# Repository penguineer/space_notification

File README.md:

netz39_space_notification
=========================

Teilprojekte der Space Notification, z.B.

  * Ansteuerung Außenlampe
  * Ampel
  * Twitter-Notification

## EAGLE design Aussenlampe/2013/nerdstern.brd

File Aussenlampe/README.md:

netz39_space_notification
=========================

Außenlampe wird von Rene angeschlossen

Hier: Entwicklung des Steuerboards.

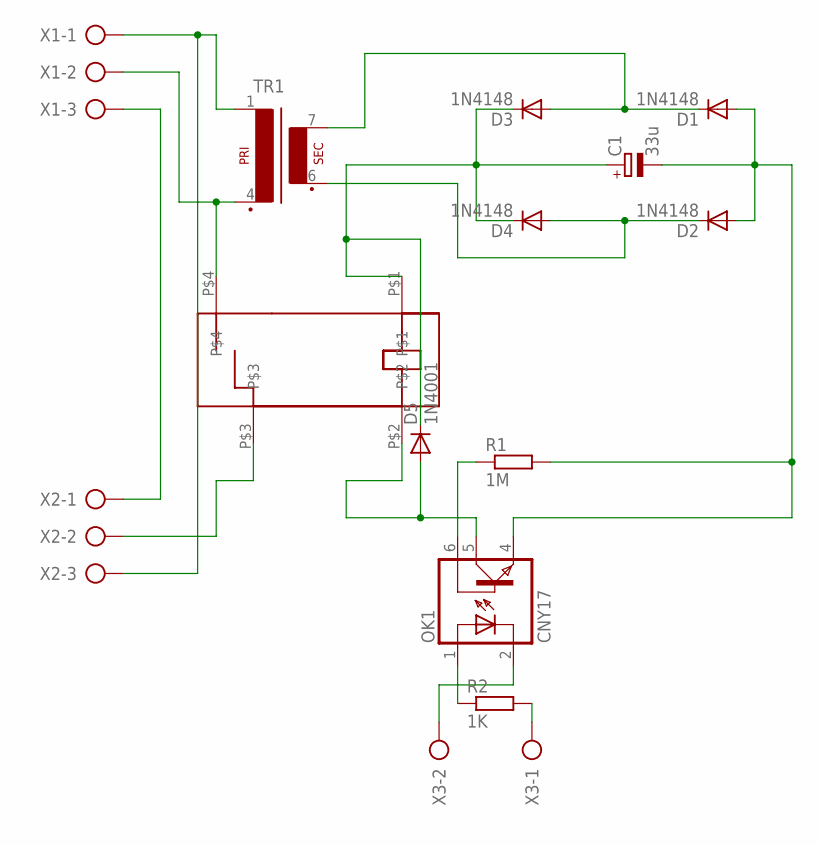
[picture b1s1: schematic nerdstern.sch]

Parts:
C1: 33u; E2-5
D1, D2, D3, D4: 1N4148; DO35-7
D5: 1N4001; DO35-7
OK1: CNY17; DIL06
R1: 1M; 0204/5
R2: 1K; 0204/5
TR1: EE20-1
U$1: JS_05_MN_KT
X1, X2: AK500/3
X3: AK500/2

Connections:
GND: C1.-, D1.A, D2.A, OK1.4 (EMI), R1.2
GND2: X1.3, X2.1
unnamed: TR1.4 (P2), U$1.P$4, X1.2
unnamed: U$1.P$3, X2.2
unnamed: TR1.1, X1.1, X2.3
unnamed: D1.C, D3.A, TR1.7 (S4)
unnamed: C1.+, D3.C, D4.C, D5.C, U$1.P$1
unnamed: D5.A, OK1.5 (COL), U$1.P$2
unnamed: D2.C, D4.A, TR1.6 (S3)
unnamed: OK1.1 (A), R2.1
unnamed: OK1.2 (C), X3.2
unnamed: OK1.6 (BAS), R1.1
unnamed: R2.2, X3.1

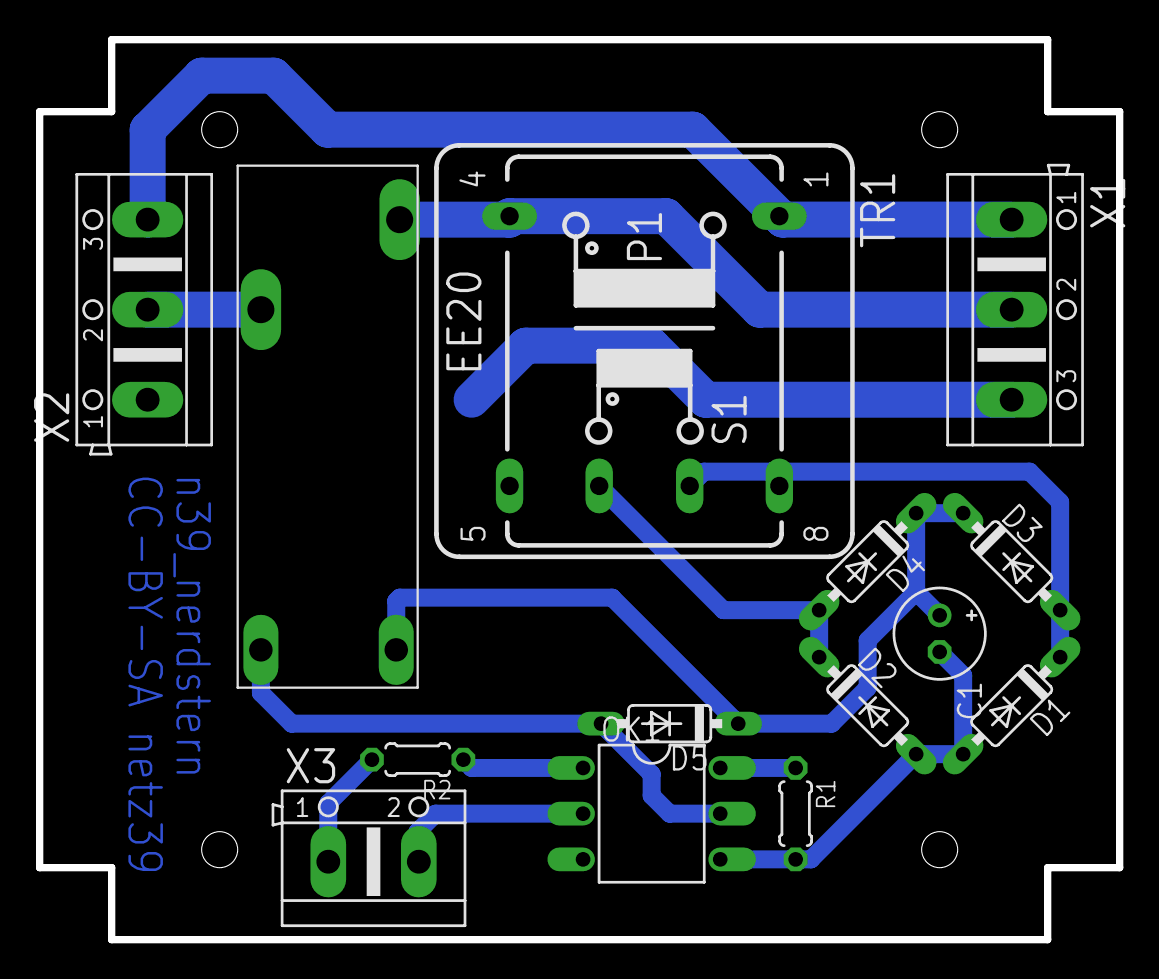
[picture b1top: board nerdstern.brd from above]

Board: 2 copper layers, 60.0 x 50.0 mm, 14 parts (0 on the bottom side), 13 nets.

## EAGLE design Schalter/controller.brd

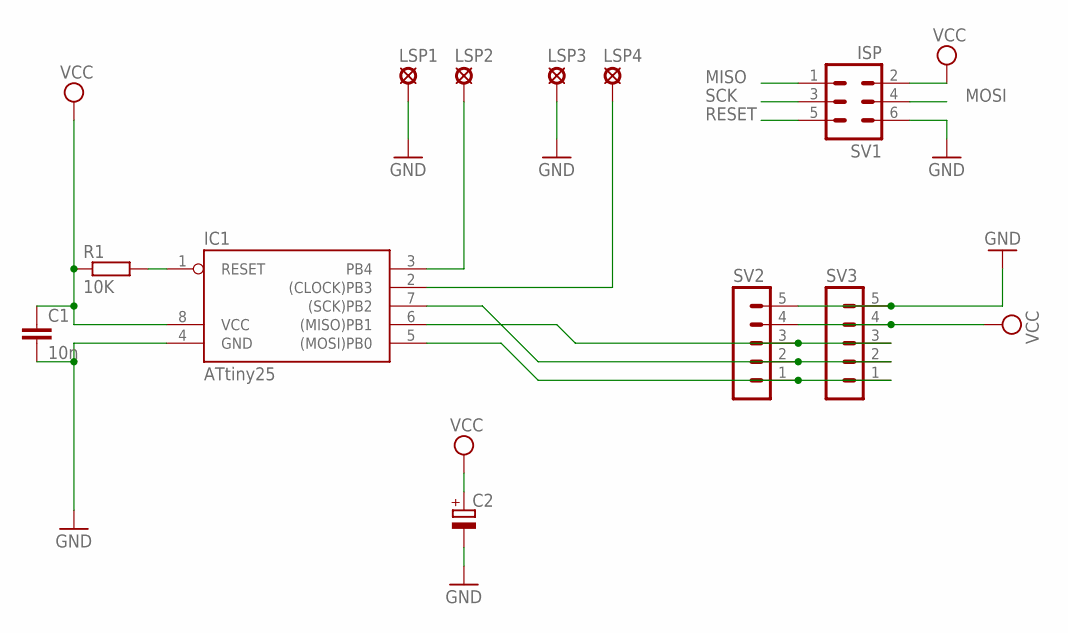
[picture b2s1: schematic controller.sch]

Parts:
C1: 10n; C025-024X044
C2: CPOL-EUE2.5-6; E2,5-6
IC1: ATtiny25; DIL08
LSP1, LSP2, LSP3, LSP4: SE11
R1: 10K; 0207/7
SV1: ISP; MA03-2
SV2, SV3: MA05-1

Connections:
GND: C1.2, C2.-, IC1.4 (GND), LSP1.MP, LSP3.MP, SV1.6, SV2.5, SV3.5
MISO: IC1.6 ((MISO)PB1), SV1.1, SV2.3, SV3.3
MOSI: IC1.5 ((MOSI)PB0), SV1.4, SV2.1, SV3.1
unnamed: IC1.3 (PB4), LSP2.MP
unnamed: IC1.2 ((CLOCK)PB3), LSP4.MP
RESET: IC1.1 (RESET), R1.2, SV1.5
SCK: IC1.7 ((SCK)PB2), SV1.3, SV2.2, SV3.2
VCC: C1.1, C2.+, IC1.8 (VCC), R1.1, SV1.2, SV2.4, SV3.4

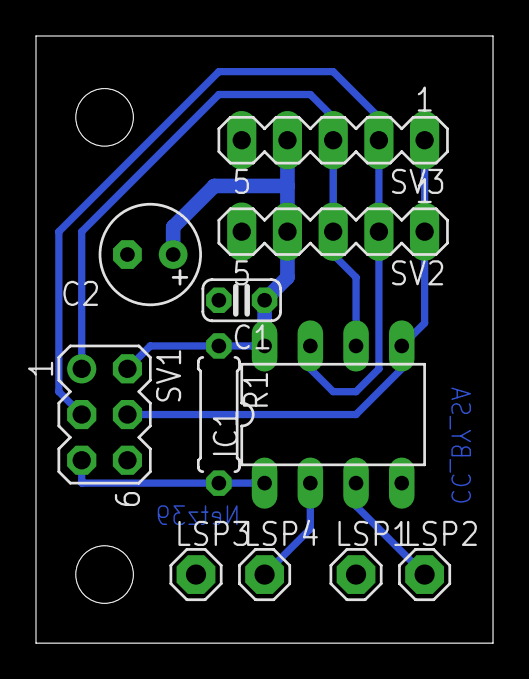
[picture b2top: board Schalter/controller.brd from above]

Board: 2 copper layers, 25.4 x 33.7 mm, 11 parts (0 on the bottom side), 8 nets.

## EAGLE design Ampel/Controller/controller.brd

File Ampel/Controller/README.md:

Ampel
=========================

Aktueller Stand:

Ampel hängt an der Wand, Controller hat einfache Firmware.

Belegung des Steuerkabels:

schwarz – Masse
blau    – Blink-Attribut
gelb    – Rot
grün    – Grün

Die Steuerleitungen liegen per Pull-Up auf 5V und müssen zum Aktivieren nach Masse gezogen werden (Vorwiderstand nicht nötig).

Ansteuerung per Raspy: 
Derzeit GPIO 17 -> rot
        GPIO 18 -> grün

Rechnername wittgenstein

http://wittgenstein/{red, green, none}

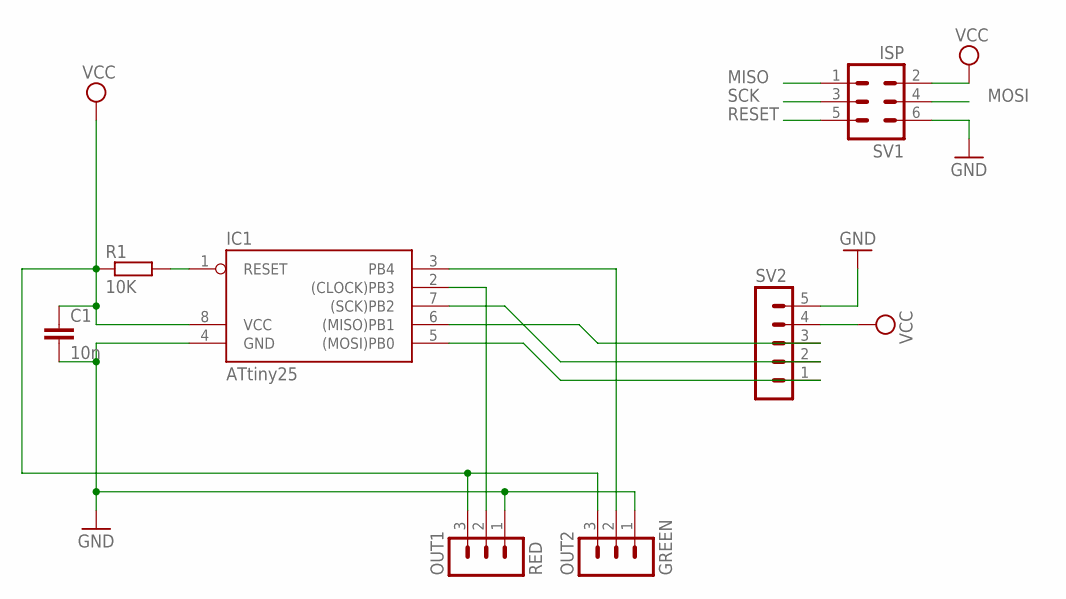
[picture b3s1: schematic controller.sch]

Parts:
C1: 10n; C025-024X044
IC1: ATtiny25; DIL08
OUT1: RED; MA03-1
OUT2: GREEN; MA03-1
R1: 10K; 0207/7
SV1: ISP; MA03-2
SV2: MA05-1

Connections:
GND: C1.2, IC1.4 (GND), OUT1.1, OUT2.1, SV1.6, SV2.5
MISO: IC1.6 ((MISO)PB1), SV1.1, SV2.3
MOSI: IC1.5 ((MOSI)PB0), SV1.4, SV2.1
unnamed: IC1.3 (PB4), OUT2.2
unnamed: IC1.2 ((CLOCK)PB3), OUT1.2
RESET: IC1.1 (RESET), R1.2, SV1.5
SCK: IC1.7 ((SCK)PB2), SV1.3, SV2.2
VCC: C1.1, IC1.8 (VCC), OUT1.3, OUT2.3, R1.1, SV1.2, SV2.4

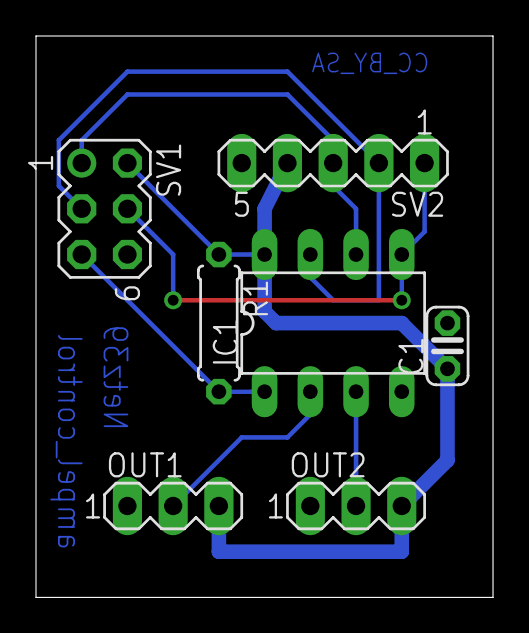
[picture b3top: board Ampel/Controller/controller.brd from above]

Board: 2 copper layers, 25.4 x 31.2 mm, 7 parts (0 on the bottom side), 8 nets.

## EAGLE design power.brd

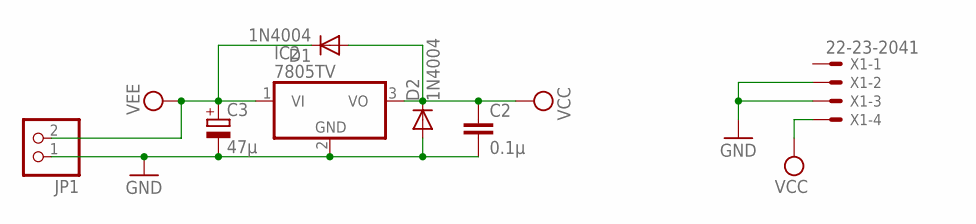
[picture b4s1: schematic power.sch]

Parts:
C2: 0.1µ; C025-024X044
C3: 47µ; E5-4
D1, D2: 1N4004; DO41-10
IC2: 7805TV; TO220V
JP1: PINHD-1X2; 1X02
X1: 22-23-2041

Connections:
GND: C2.2, C3.-, D2.A, IC2.2 (GND), JP1.1, X1.2, X1.3
VCC: C2.1, D1.A, D2.C, IC2.3 (VO), X1.4
VEE: C3.+, D1.C, IC2.1 (VI), JP1.2

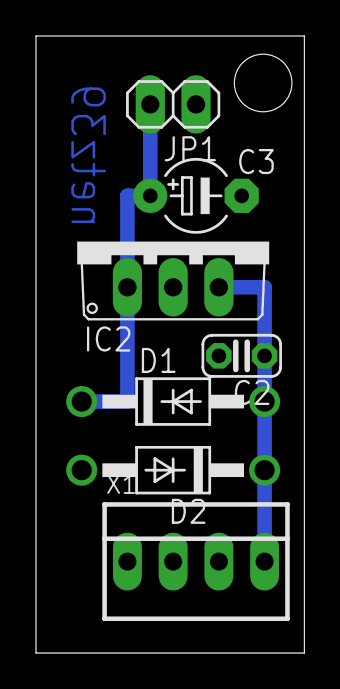
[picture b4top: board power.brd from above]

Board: 2 copper layers, 14.9 x 34.3 mm, 7 parts (0 on the bottom side), 3 nets.

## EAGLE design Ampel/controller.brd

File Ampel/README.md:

Ampel
=========================

Aktueller Stand:

Ampel steht im Space, kann per Stecker angeschlossen werden.

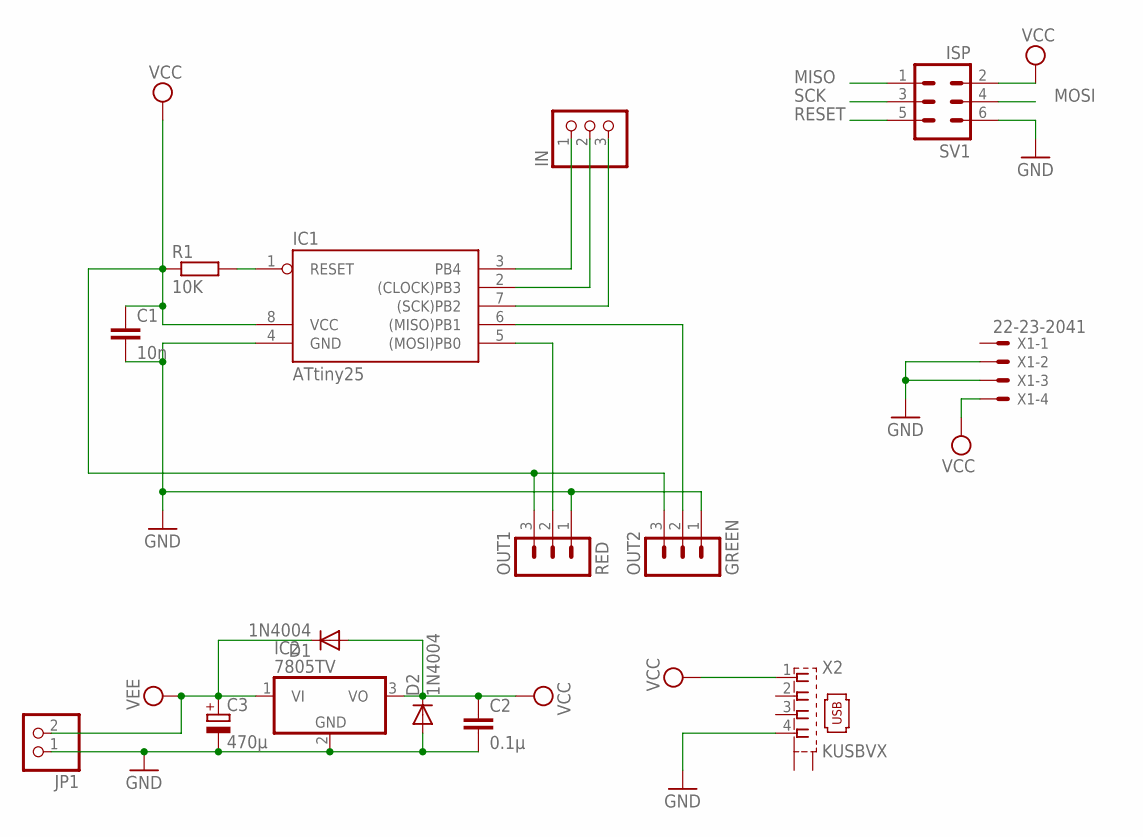
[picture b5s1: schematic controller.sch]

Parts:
C1: 10n; C025-024X044
C2: 0.1µ; C025-024X044
C3: 470µ; E5-4
D1, D2: 1N4004; DO41-10
IC1: ATtiny25; DIL08
IC2: 7805TV; TO220V
IN: PINHD-1X3/90; 1X03/90
JP1: PINHD-1X2; 1X02
OUT1: RED; MA03-1
OUT2: GREEN; MA03-1
R1: 10K; 0207/10
SV1: ISP; MA03-2
X1: 22-23-2041
X2: KUSBVX

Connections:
GND: C1.2, C2.2, C3.-, D2.A, IC1.4 (GND), IC2.2 (GND), JP1.1, OUT1.1, OUT2.1, SV1.6, X1.2, X1.3, X2.4
MISO: IC1.6 ((MISO)PB1), OUT2.2, SV1.1
MOSI: IC1.5 ((MOSI)PB0), OUT1.2, SV1.4
unnamed: IC1.2 ((CLOCK)PB3), IN.2
unnamed: IC1.3 (PB4), IN.1
RESET: IC1.1 (RESET), R1.2, SV1.5
SCK: IC1.7 ((SCK)PB2), IN.3, SV1.3
VCC: C1.1, C2.1, D1.A, D2.C, IC1.8 (VCC), IC2.3 (VO), OUT1.3, OUT2.3, R1.1, SV1.2, X1.4, X2.1
VEE: C3.+, D1.C, IC2.1 (VI), JP1.2

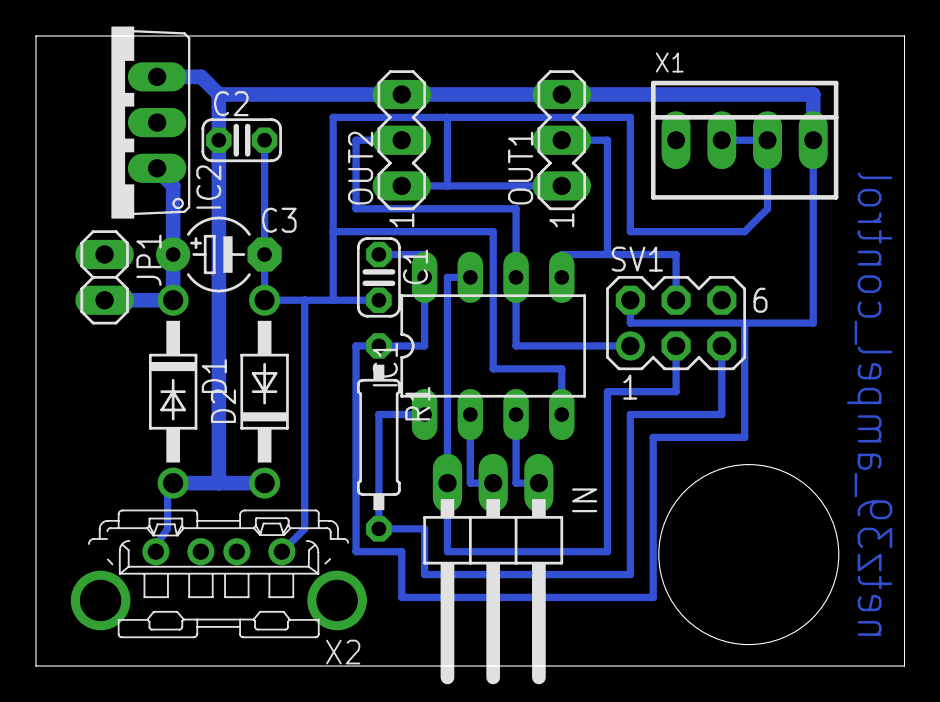
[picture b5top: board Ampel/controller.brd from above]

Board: 2 copper layers, 48.2 x 35.0 mm, 15 parts (0 on the bottom side), 9 nets.

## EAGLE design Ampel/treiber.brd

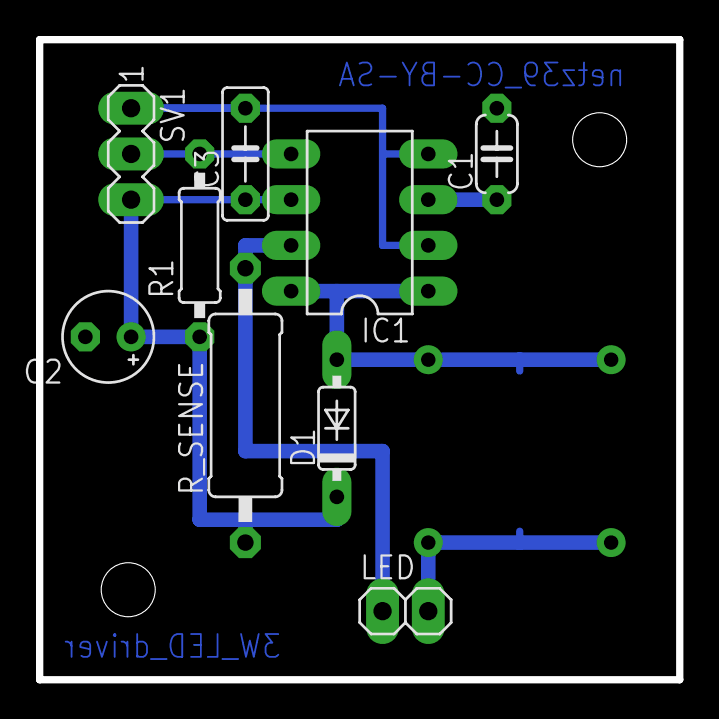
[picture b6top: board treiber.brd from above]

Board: 2 copper layers, 35.6 x 35.6 mm, 10 parts (1 on the bottom side), 7 nets.

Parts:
C1: 330p; C050-024X044
C2: 68µ; E2,5-5
C3: 100n; C5B2.5
D1: MBRS240; DO35-7
IC1: MC34063AP; DIL08
L1: 220µ; DR1030
LED: 3W; 1X02
R1: 4.7K; 0207/10
R_SENSE: 0.18R; 0411/15
SV1: Control; MA03-1

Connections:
GND: C1.2, C2.-, C3.2, IC1.2, IC1.4, SV1.1
unnamed: C1.1, IC1.3
unnamed: D1.A, IC1.1, IC1.8, L1.2
unnamed: IC1.7, LED.1, R_SENSE.2
unnamed: L1.1, LED.2
PWM: IC1.5, R1.2, SV1.2
VCC: C2.+, C3.1, D1.C, IC1.6, R1.1, R_SENSE.1, SV1.3

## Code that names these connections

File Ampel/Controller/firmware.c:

/*
 * Ampel-Controller mit I²C-Anbindung
 * Autor: Stefan Haun <tux@netz39.de>
 * 
 * Entwickelt für ATTINY25
 * 
 * nutzt https://github.com/eriksl/usitwislave.git
 * 
 * DO NOT forget to set the fuses s.th. the controller uses the 8 MHz clock!
 */


/* define CPU frequency in MHz here if not defined in Makefile */
#ifndef F_CPU
#define F_CPU 8000000UL
#endif

#include <avr/io.h>
#include <avr/interrupt.h>
#include <util/delay.h>
#include <util/twi.h>
#include <stdint.h>

#include "usitwislave.h"

#define LED_INTERNAL
//#define LED_EXTERNAL


inline void setPortB(char mask) {
  PORTB = PORTB | mask;
}

inline void resetPortB(char mask) {
  PORTB = PORTB & ~mask; 
}

const uint8_t COLOR_NONE  = 0;
const uint8_t COLOR_RED   = 1;
const uint8_t COLOR_GREEN = 2;

volatile uint8_t current_color;
volatile uint8_t is_blink;

inline void switch_color(uint8_t col) {
#ifdef LED_INTERNAL
   resetPortB(0b11000);
   if (col == COLOR_RED) 
     setPortB(0b10000);
   if (col == COLOR_GREEN) 
     setPortB(0b01000);
#endif
#ifdef LED_EXTERNAL
   setPortB(0b11000);
   if (col == COLOR_RED)
       resetPortB(0b10000);
   if (col == COLOR_GREEN)
       resetPortB(0b01000);
   #endif
}

inline void setColor(const uint8_t col, const uint8_t blink) {
  current_color = col;
  is_blink = blink;
  //switch_color(col);
}

//flag state change
inline void i3c_stateChange() {
  // port B1 as output
  DDRB |= (1 << PB1);
  // set to low
  PORTB &= ~(1 << PB1);
}

// put to listening mode
inline void i3c_tristate() {
  // port B1 as input
  DDRB &= ~(1 << PB1);
  // no pull-up
  PORTB &= ~(1 << PB1);
}

inline uint8_t i3c_state() {
  return (PINB & (1 << PB1)) >> PB1;
}

/*
 * I²C Datenformat:
 * 
 * PCCCDDDD
 * 
 * parity (P)
 * command (CCC)
 * 	GetLight 0x01   Aktuellen Datenwert ausgeben
 *      SetLight 0x02   Neuen Datenwert setzen
 * 
 * data (DDDD)
 * 	1 bit blink-Status
 * 	3 bit Farbe:	0 keine
 * 			1 rot
 * 			2 grün
 */
#define CMD_I3C_RESET 0x00
#define CMD_GETLIGHT  0x01
#define CMD_SETLIGHT  0x02

static void twi_callback(uint8_t buffer_size,
                         volatile uint8_t input_buffer_length, 
                         volatile const uint8_t *input_buffer,
                         volatile uint8_t *output_buffer_length, 
                         volatile uint8_t *output_buffer) {
  
  if (input_buffer_length) {
    const uint8_t parity = (input_buffer[0] & 0x80) >> 7;
    const uint8_t cmd  = (input_buffer[0] & 0x70) >> 4;
    const uint8_t data = input_buffer[0] & 0x0F;
    
    // check parity
    uint8_t v = input_buffer[0] & 0x7F;
    uint8_t c;
    for (c = 0; v; c++)
      v &= v-1;
    c &= 1;
    
    // some dummy output value, as 0 states an error
    uint8_t output=0;
    
    // only check if parity matches
    if (parity == c)
    switch (cmd) {
      case CMD_I3C_RESET: {
	i3c_tristate();
	break;
      }
      case CMD_GETLIGHT: {
	const uint8_t state = ((is_blink == 0 ? 0 : 1) << 4) + current_color;
	output = state;

	// set msb to avoid error state
	output += 0x80;
	
	break;
      }
      case CMD_SETLIGHT: {
	setColor(data&0x7, data&0x8);
	output = 1;
	break;
      }
    }

    *output_buffer_length = 2;
    output_buffer[0] = output;
    output_buffer[1] = ~(output);    
  }  
}

static void twi_idle_callback(void) {
  // void
}

void init(void) {
  /*
   * Pin-Config PortB:
   *   PB0: I2C SDA
   *   PB1: I3C INT
   *   PB2: I2C SDC
   *   PB3: Rt (Out)
   *   PB4: Gn (Out)
   */
  DDRB  = 0b1111010;
  // PullUp für Eingänge
  PORTB = 0b11111010;

  /*
   * Set state: no color
   */
  setColor(COLOR_NONE, 0);

   
   /*  disable interrupts  */
   cli();
   
   
   /*  set clock   */
  CLKPR = (1 << CLKPCE);  /*  enable clock prescaler update       */
  CLKPR = 0;              /*  set clock to maximum                */

  /*  timer init  */
  TIFR &= ~(1 << TOV0);   /*  clear timer0 overflow interrupt flag    */
  TIMSK |= (1 << TOIE0);  /*  enable timer0 overflow interrupt        */

  /*  start timer0 by setting last 3 bits in timer0 control register B
   *  to any clock source */
  //TCCR0B = (1 << CS02) | (1 << CS00);
  TCCR0B = (1 << CS00);

    
  // Global Interrupts aktivieren
  sei();  
  
  i3c_tristate();
}

int main(void)
{
  // initialisieren
  init();

  // start TWI (I²C) slave mode
  usi_twi_slave(0x20, 0, &twi_callback, &twi_idle_callback);

  return 0;
}

const int TCOUNT_MAX = 20000;
volatile uint16_t tcount = 0;
volatile uint8_t blink = 0;

ISR (TIMER0_OVF_vect)
{
  // TODO be a bit more fancy at this point
  tcount++;
  if (tcount > TCOUNT_MAX) {
    tcount = 0;
    blink = !blink;
    switch_color(is_blink && !blink ? COLOR_NONE : current_color);
  }
}

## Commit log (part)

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2013-02-10 Beschreibung Teilprojekte
2013-02-10 Teilprojekte Ampel, Aussenlampe; README-Files
2013-02-11 Scan des Schaltungsentwurfs, mit einer Grobskizze für das Leiterplattenlayout
2013-02-13 Stückliste für die Steuerung der Außenlampe
2013-02-21 schematic and board layout done, routing missing
2013-02-21 Update Stückliste
2013-02-21 Entwurf Stückliste
2013-02-21 Kopie Schaltplan aus http://www.mikrocontroller.net/articles/Konstantstromquelle_fuer_Power_LED
2013-02-21 Datenblatt Schaltregler
2013-02-22 add optocopler, wirin still questionable
2013-02-28 routing and some repositioning of parts
2013-02-28 .pdf for penguineer
2013-02-28 schaltplan korrigiert
2013-03-01 routing
2013-03-01 add cc-license on board
2013-03-02 modify writing on board
2013-03-13 Eagle-Libraries für das Board
2013-03-13 Schaltplan und Board LED-Treiber
2013-03-14 Kleine Anpassung routing für mehr Massefläche
2013-03-14 add git ignore list with automatically created eagle backup files
2013-03-14 Pad-Größen und Leiterbahnbreiten angepasst
2013-03-14 Noch ein wenig Layout-Tuning in der LED-Treiberschaltung
2013-03-14 R_SENSE angepasst
2013-03-14 Schaltung nochmal angepasst
2013-03-14 entwurf controller
2013-03-15 spannungsregler
2013-03-15 some routing
2013-03-15 Jumper für Stromversorgung und Spannungsregler angepasst
2013-03-15 Schaltung und Board Spannungsversorgung
2013-03-15 Ladekondensatoren angepasst
2013-03-15 Controller und Treiber für die Ampel in verschiedene Verzeichnisse gelegt
2013-03-16 Erste Version Firmware: rot/grün-Schaltung über INPUT
2013-03-16 .gitignore für firmware-files
2013-03-16 überflüssigen Code entfernt
2013-03-16 Doku Anschlussbelegung Ampel
2013-03-16 Readme wieder ins Ampel-Verzeichnis
2013-03-16 Erweiterung Firmware: blinken
2013-03-17 Stecker angepasst
2013-03-27 Space-API-Script
2013-03-28 SpaceAPI-Sachen in eigenem Verzeichnis
2013-03-28 Neuer (provisorischer) Schildentwurf
2013-04-03 Howto SpaceStatus v1
2013-04-03 Howto SpaceStatus v2
2013-04-14 Added a TWI library and TWI control support.
2013-04-15 Code makeover in firmware: comments, added TODOs, some minor code additions and move-arounds
2013-04-16 I²C-Kommandos, tests pending
2013-04-20 Operator-Precendence fixed
2013-04-20 gitignore angepasst für twi-lib object file
2013-04-20 kleine Anpassungen
2013-04-20 Redesign des Controller-Boards auf I2C
2013-04-20 Anpassung an Anschluss vom I2C-Adapter
2013-04-20 I2C-Adapter
2013-04-20 letzte Anpassungen zum Ätzen
2013-04-22 Redesign (INT-Leitung und breitere Leitung für Spannungsversorgung)
2013-04-24 Adapter: stecker angepasst Controller: board redesign
2013-05-05 Gehäuse für den Ampelcontroller
2013-05-05 trove für den i2c-adapter
2013-05-05 Gehäusedesign v2
2013-05-05 Kleine Anpassungen im SCAD-Script
2013-05-05 trove Ampel-Controller v2
2013-05-05 trove v3
2013-05-06 modified .gitignore
2013-05-06 rm nerdstern.pdf
2013-05-06 anpassung an i2c-board
2013-05-06 kräftigeres Gehäuse und Snapper
2013-05-08 Angepasstes Trove für den Controller
2013-10-14 new buttons
    font und farben in absprache mit eriu
2013-10-14 let inkscape save its stuff
2013-10-14 adapt colors and export smaller png
2013-10-15 make logo a little smaller
2013-10-24 pending changes
2014-01-03 i3c-handling
2014-01-03 spaceapi-Script ausführbar gemacht
2014-01-03 Controller-Trove: fine-tuning für Controller-Board Anpassung Build-Umgebung
2014-01-03 aktuelle Ampel-Files
2014-02-26 remove unneeded files
2014-02-26 ReadMe für Ampel-Adapter
2014-02-26 I²C-Adapter ist nun in https://github.com/netz39/i2cbridge
2014-05-19 Check for space status before tweeting
2014-05-19 Fixed the Space API query location (actually: do the query before the change! :oops: )
2014-05-22 Changed I2C to the I3C protocol to gain compatibility with other devices and the xmppsc.
2014-05-22 Fixed some data types.
2014-05-23 Changed the programmer
2014-07-04 Schalter: Schematics für Schalter-Controller (adaptiert vom Ampel-Controller)
2014-07-13 Schalter: Ladekondensator eingefügt
2014-07-13 Schalter: Board dimensions
2014-07-13 Schalter: USI-TWI-Lib
2014-07-13 Schalter: Firmware
2014-10-10 Spacetime-Schalter nutzt nun doch attiny85
2014-10-10 Spacetime-Schalter: Halterung für Controller mit Wandabstandshalter
2014-10-10 Spacetime-Schalter: Halterung für Buchse mit Wandabstandshalter
2014-10-17 Schalter: Grundplatte, Freecad-Version
2014-10-17 Schalter: Korrigiertes DXF der Grundplatte
    (FreeCad hat iwie Probleme mit der Richtung von Kreisbögen; mit LibreCad korrigiert.)
2014-10-18 Schalter: Added fuse target to Makefile
2014-10-18 Schalter: Bugfixes in the firmware
2014-10-18 Schalter: Switch-Ports getauscht, ist in der Hardware jetzt doch anders herum verlötet.
2014-10-18 Schalter: Fix für #4
    *hust* :oops:
2014-10-18 color.sh mit i3c-Client-Aufrufen
2014-10-18 Provisorisches™ Script für SpaceStatus-Steuerung über den Schalter
2014-10-22 Schalter: Daten von der Fräse
2016-08-08 Adapt statusswitch to ipv6
2016-08-09 MQTT: Pass 1 - Switch Lights pased on SpaceAPI and Door
2017-02-04 Refine the countdown condition
2017-02-04 MQTT Pass 2 - publish lever state to topic
    See http://www.netz39.de/wiki/projects:2014:gatekeeper:mqtt#topic
    Relevant topics are
    Netz39/Things
    StatusSwitch
    Lever
    State ("open", "closed", "neutral")
2019-01-01 New Ampel controller, first draft
2019-01-06 Fix dimensions
2019-01-06 Outline and mounting holes
2019-01-13 Move upper LED
2019-01-25 Fix Attiny85 footprint
    Change to the attiny we actually have (Attiny85V-10 SU)
2019-03-23 Adapt Makefile for attiny85 and add fuse setting
2019-03-23 Adapt firmware to new LED behaviour
2019-05-05 Add python script to update SpaceAPI with added functionality (door status). The script subscribes to the revelant MQTT topics and pushes updates on new messages. Requirements: Python 3, paho-mqtt pa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
2019-05-12 add beautiful argparse command line interface
2019-05-17 add picture symlink creation & bugfix
2019-05-24 split into two image paths
2019-05-24 remove unnecessary print
2019-05-30 Move spaceapi script to non-www directory
2019-05-30 Adapt standard locations
2019-10-19 spaceapi: template: Minor corrections
    * Add root resource to website URL
    * Twitter handle is lower case
    * Add newline to end of file (jq does that and my editor as well)
2019-10-19 spaceapi: template: Replace "irc" with "jabber"
    Our IRC channel is more or less dead, we use XMPP MUC for a while now.
    This is consistent with what we announce on our website:
    http://www.netz39.de/verein/kommunikation/
2019-10-19 spaceapi: template: Add website feeds
    Add our blog and calendar feeds.
2020-12-08 Disable tweet action
2020-12-08 Add a sign for status "occupied"
2020-12-08 Link to "occupied" instead of "open"
2020-12-08 Export occupied.svg to PNG
2020-12-08 Set open-logo to "occupied" in JSON template
2020-12-08 Make occupied sign available to status
2020-12-08 SpaceAPI: Improve spacing for occupied banner
    This has the same margins as the 'closed' banner now.
2020-12-13 Use more recent usitwislave library
2021-11-07 Start processing I2C data after first byte
    RPi2 stopped sending stop conditions between frames of an I2C request
    (repeated start), which means this library does not detect the step
    between sending data and expecting a processed result.
    As we only ever send one byte of data, it is safe for now to process the
    buffer after the first byte to have the result ready when it is expected.
2022-09-27 Switch to HTTPS
2022-09-27 Change icon for "open" state from occupied to open
2022-09-28 :alien: SpaceApi: Change URL to avoid redirect
    Our wiki has moved into a container and to another URL. HTTP requests to
    the old URL are answered with a status code 301 (Moved Permanently).
    To avoid that extra request, point directly to the new URL.
2022-12-08 Move nerdstern EAGLE files to own folder
2022-12-08 Add new schematic/pcb to control Nerdstern with SSR
2022-12-09 Add ReadMe to Nerdstern v2 (2022)
2024-11-01 Fix subscription topics for door and space status lever
2024-11-02 Revamp ledcontrol to control the LEDs from MQTT topic
2024-11-02 Apply RPi2 I2C communication fix for switch
    Apply the fix from https://github.com/netz39/space_notification/pull/12
    to the switch firmware.
2024-11-02 remove spaceapi folder after move to Netz39AmpelController and Netz39SpaceAPI-Service

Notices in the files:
Aussenlampe/2013/nerdstern.brd:
CC-BY-SA netz39
